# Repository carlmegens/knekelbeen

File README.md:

# Knekelbeen 💀

Een pratende Halloween-schedel die in de slingerkast van een oude wandklok
woont. Hij praat in het Nederlands met de kinderen aan de deur, beweegt zijn
kaak mee met wat hij zegt, kijkt rond, laat zijn ogen gloeien en zet de kaarsen
om hem heen aan het flakkeren. Komt er iemand aan, dan begroet hij die zelf.

```
 kinderen ──► microfoon in de klok ──► schedel (ESP32-S3) ──wifi──► laptop-app ──► Gemini Live
                                            ▲                                          │
 kaak · ogen · kaarsen · nek ◄── speaker ◄──┴──────────── stem (audio over UDP) ◄──────┘
```

De schedel zelf doet de hardware: geluid afspelen, de servo's, de leds, de
microfoon en de sensor. Het denken gebeurt in de laptop-app, die het geluid
doorstuurt naar Gemini en het antwoord terugstuurt naar de schedel. Zonder
laptop werkt hij ook: dan speelt hij de clips van de SD-kaart af.

## Wat hij kan

- **Praten met de AI:** Gemini Live hoort de kinderen en antwoordt meteen
  hardop. Je kunt kiezen uit de Gemini-stemmen of de zelf ontworpen stem
  "Knekelbeen". Zijn karakter staat in [`brain/persona.txt`](brain/persona.txt),
  zijn moppen in [`brain/jokes.txt`](brain/jokes.txt). Hij luistert alleen naar
  Nederlands en weet dat kinderen niet altijd duidelijk praten.
- **Kaak:** volgt het volume van de stem, met een zachte veerbeweging zodat hij
  niet tegen de aanslag klapt.
- **Hoofd draaien:** kijkt af en toe opzij tijdens het praten.
- **Ogen en kaarsen:** WS2812-ogen en een snoer WS2801-kaarsen die meeflakkeren
  met de stem. Een extra ledje of ledstrip kan op LED 2.
- **Soundboard:** clips en geluidseffecten (klokslag, middernacht, onweer,
  wind, hartslag, krakende deur, uil) op de SD-kaart, met een knop per geluid.
  Effecten (`fx_*.wav`) bewegen de kaak niet.
- **Bezoekers merken:** een PIR- of radarsensor op de PIR-aansluiting laat de
  ogen flitsen en de AI een groet uitspreken.
- **Eigen microfoon:** een INMP441 in de klok, zodat de laptop niet bij de deur
  hoeft te staan.

## Hardware

Een eigen printplaat ([`pcb/`](pcb/)) met een ESP32-S3-DevKitC-1 (N8R8) erop
geprikt. Alles wat van de print af gaat, zit aan een schroefklem.

| Onderdeel | Pin(nen) | Aansluiting |
|---|---|---|
| Kaakservo | GPIO 4 | KAAK |
| Draaiservo (nek) | GPIO 8 | DRAAI |
| Ogen, WS2812 | GPIO 15 | OGEN |
| Kaarsen, WS2801 | data 11, klok 12 | KAARSEN |
| LED 2, WS2812 | GPIO 48 | LED 2 |
| PIR of radar | GPIO 2 (hoog = beweging) | PIR |
| 2× versterker DFR0954 (I2S) | BCLK 5, LRC 6, DIN 7; aan/uit 10 (L) en 9 (R) | SPEAKER L/R |
| Microfoon INMP441 (I2S) | WS 16, SCK 17, SD 18 | MIC |
| microSD (SPI) | SCK 13, MISO 14, MOSI 21, CS 47 | op de print |

**De schedel** is de [Robot Skull (Like Geoff off Craig Ferguson)](https://www.printables.com/model/471773-robot-skull-like-geoff-off-craig-ferguson)
van Geoff Williams op Printables (CC BY-SA). Op ware grootte geprint is hij
8,4 cm breed, 11,5 cm diep en 9,4 cm hoog: ongeveer half zo groot als een echte
schedel. Alleen de schedel en de wervel zijn geprint.

De pinnen staan in [`firmware/include/config.h`](firmware/include/config.h).
Voeding: een aparte 5 V-voeding voor de versterkers, servo's en leds.

## In de repo

| Map | Wat |
|---|---|
| [`firmware/`](firmware/) | PlatformIO-project voor de ESP32-S3, inclusief de webpagina van de schedel |
| [`brain/`](brain/) | De laptop-app: bediening, AI (Gemini Live, of Whisper + Claude + Piper) |
| [`clips/`](clips/) | De clips en geluidseffecten, met de teksten in `lines.txt` |
| [`tools/`](tools/) | Clips maken, effecten synthetiseren, uploaden, de microfoon testen |
| [`pcb/`](pcb/) | De printplaat (KiCad, door scripts gegenereerd) en de gerbers |
| [`case/`](case/) | Het geprinte kastje voor de print (OpenSCAD) |
| [`kaarsen/`](kaarsen/) | De geprinte kaarsen voor de WS2801-ledjes |
| [`nek/`](nek/) | De draaiende nek: Fusion-ontwerp, STL's, schroeven en montage |
| [`radar/`](radar/) | ESPHome-config voor de Seeed MR24HPC1-radar als bezoekerssensor |
| [`docs/`](docs/) | De ontwerpopdracht voor de nek, ideeën en het camera-plan |
| `voices/` | Piper-stemmen (niet in git) en de ID van de ontworpen Gemini-stem |

## Aan de slag

### 1. Firmware

Zet je wifi in `firmware/include/secrets.h`; kopieer daarvoor
`secrets.example.h`. Lukt verbinden niet, dan start de schedel een eigen
netwerk `TalkingSkull`.

```
python -m venv .venv && .venv/bin/pip install platformio
cd firmware
../.venv/bin/pio run -e usb -t upload    # de eerste keer, via de native USB-poort
../.venv/bin/pio run -e ota -t upload    # daarna via wifi
```

Daarna is de schedel te bedienen op `http://skull.local` (of zijn IP-adres).
Meer, ook over flashen en Tailscale, in [`firmware/README.md`](firmware/README.md).

### 2. Laptop-app

```
.venv/bin/pip install aiohttp anthropic google-genai numpy faster-whisper piper-tts
echo 'GEMINI_API_KEY=...' > .env         # nooit committen
.venv/bin/python brain/app.py            # of: systemctl --user start skull-brain
```

Open `http://localhost:8000`. De browser staat de microfoon alleen toe op
localhost, daarom draait de bediening met AI op de laptop. Met `SKULL=<ip>`
wijs je een andere schedel aan.

Handige omgevingsvariabelen: `SKULL_GEMINI_MODEL`, `SKULL_GEMINI_VOICE`,
`SKULL_WHISPER` en voor de Claude-modus `ANTHROPIC_API_KEY`. Met
`SKULL_CAM` en `SKULL_CAM_KEY` (een Thingino-camera bij de deur) ziet
Knekelbeen de kinderen bij de begroeting; zie
[`docs/vision-plan.md`](docs/vision-plan.md).

### 3. Clips en effecten

```
tools/gemini_clip.py welkom "Welkom, kleintjes..." --style "fluisterend" --upload
tools/gemini_clip.py --batch clips/lines.txt --upload   # alles uit lines.txt
tools/make_fx.py --upload                               # de geluidseffecten
tools/upload.sh clips/iets.wav                          # een los bestand
tools/make_cues.py --upload                             # lichteffecten in de clips
```

Clips brengen hun eigen lichteffecten mee: `clips/cues.txt` zegt per clip
wanneer de kaarsen opflakkeren, uitgaan of spookgroen worden, wanneer de ogen
flitsen en wanneer de bliksem inslaat (`bliksem`: één inslag, `donder`: een
rollend onweer over kaarsen, ogen en LED 2). `make_cues.py` vindt die zelf (op woorden als "boe" en "geest", en op
de klappen in de geluidseffecten); pas het bestand gerust met de hand aan.
Upload een nieuwe of aangepaste clip daarna met `make_cues.py --upload <naam>`,
anders speelt hij zonder effecten.

Clips worden opgeslagen als 22,05 kHz mono en op loudness genormaliseerd.

### 4. Instellingen bewaren

```
tools/settings.py              # wat staat aan en uit
tools/settings.py --save       # alles naar config/instellingen.json
tools/settings.py --restore    # en weer terug, bijvoorbeeld na een nieuwe flash
```

### 5. Microfoon testen

```
tools/mic_test.py            # 4 s stil, dan 6 s praten: ruis, verschil, storingen
```

Boven de 25 dB verschil tussen spraak en ruis is prima.

## Twee bedieningspagina's

De schedel heeft een eigen pagina (`firmware/web/index.html`, ingebakken in de
firmware) en de laptop-app heeft er een (`brain/index.html`). Elke instelling
hoort op allebei. De pagina van de schedel werkt ook zonder laptop.

## Geheimen

Niet in git: `.env` (API-sleutels), `firmware/include/secrets.h` (wifi),
`radar/secrets.yaml`, de Piper-stemmodellen en eigen opnames
(`clips/opname*.wav`, `clips/raw/`).

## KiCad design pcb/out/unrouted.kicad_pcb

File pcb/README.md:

# Knekelbeen carrier board

A 100 × 96 mm, 2-layer, all through-hole board. The ESP32-S3-DevKitC-1, the
microSD module and the
DFR0954 amps plug onto it, and everything else connects with screw terminals.
The pins match `firmware/include/config.h`.

## Rebuilding

```
source kienv.sh             # only needed while KiCad isn't installed with pacman
python3 make_footprints.py  # ESP32 + DFR0954 footprints -> skull.pretty/
python3 build_board.py      # placement, nets, labels, skull art -> skull.kicad_pcb (unrouted)
python3 route.py            # Freerouting (heavy on the CPU for a few minutes), GND pour
python3 art.py              # only to redraw the skull art on an already routed board
kicad-cli pcb drc -o out/drc.rpt skull.kicad_pcb
```

`out/skull-jlcpcb.zip` holds the gerbers and drill files for ordering.

## Ordering at JLCPCB

1. Go to jlcpcb.com → **Order now** → **Add gerber file** → upload `out/skull-jlcpcb.zip`.
2. Keep the defaults: 2 layers, FR-4, 1.6 mm, HASL, 1 oz copper. Quantity 5 is the minimum.
   A colour other than green costs the same at most sizes. Black looks good on a Halloween prop.
3. Leave **PCB Assembly** off. You solder it yourself, and everything is through-hole.
4. Pick DHL/FedEx shipping for about 5–8 days. Standard shipping is cheaper but takes 2–3 weeks.

## Parts list

Checked against TinyTronics on 2026-10-13 (product codes in brackets; check
stock before ordering). `tools/tinytronics-cart.js` adds all TinyTronics parts
to your cart in one go. TinyTronics has no 3.5 mm pitch screw terminals, so
those come from Domoticx (KF350, €0.27 each) or Kiwi Electronics.

| Ref | Part | Qty | Where | Notes |
|---|---|---|---|---|
| U1 | ESP32-S3-DevKitC-1 | 1 | you have it | |
| — | Female header 40-pin, 2.54 mm | 2 | TinyTronics (40PFEMALEWHITE or -GREEN; the black 40PFEMALE was 2–4 weeks) | cut to 2× 22 for U1; the rest for the amps |
| A1, A2 | DFRobot DFR0954 amp | 2 | you have 1 | A2 can stay empty for now |
| U2 | SN74AHCT125N (DIP-14) | 1 | TinyTronics (SN74AHCT125N) | must be **AHCT** |
| — | IC socket 14-pin | 1 | TinyTronics (14PSOCKET) | |
| J3, J4, J5 | Screw terminal 2-pin, 5.08 mm | 3 | TinyTronics (2PTERM) | 5V IN, SPEAKER L, SPEAKER R |
| J6, J7, J9 | Screw terminal 3-pin, **3.5 mm** | 4 | Domoticx (KF350-3.5 3-pole) | they click together: MIC = 3+3, OGEN 3, LED 2 3 |
| J8 | Screw terminal 2-pin, **3.5 mm** | 2 | Domoticx (KF350-3.5 2-pole) | KAARSEN = 2+2 |
| J10–J13 | Male pin header 1×40, 2.54 mm | 1 | TinyTronics | cut to 3, 3, 3, 9 pins |
| — | microSD module with level shifter | 1 | TinyTronics (000375) | runs on 5 V |
| J14 | Female header 1×6, 2.54 mm, **right-angle** | 1 | Domoticx (CON-2329-P16FH, "horizontaal") | TinyTronics only has straight ones |
| F1 | PTC fuse 5 A, through-hole | 1 | TinyTronics (PPTC5000MATH) | no 4 A available; 5 A is fine. Its legs are ~10 mm apart: bend them in to the 5.1 mm footprint, and keep the body off neighbouring parts (it gets hot when tripped) |
| D1 | 1N5822 Schottky | 1 | TinyTronics (1N5822) | stripe = K |
| D2 | 1N5817 or **1N5819** Schottky | 1 | TinyTronics diode set (DIODESET, has 10× 1N5819) | stripe = K |
| C1 | 1000 µF 25 V, Ø10 mm, 5 mm pitch | 1 | TinyTronics (AISHI 1000uF 25V - 5 pieces, 008079) | mind the polarity |
| C3, C4 | 470 µF 25 V, Ø8 mm, 3.5 mm pitch | 2 | TinyTronics (AISHI 470uF 25V - 5 pieces, 008081) | mind the polarity |
| C2 | Ceramic capacitor 100 nF | 1 | TinyTronics | 5 mm holes; bend the legs if it has 2.54 mm pitch |
| R1 | Resistor 1 kΩ | 1 | TinyTronics (1kΩ 1/4W - 10 pieces, 007621) | |
| R2–R5 | Resistor 330 Ω | 4 | TinyTronics (330Ω 1/4W - 10 pieces, 007619) | |
| LED1 | LED 3 mm green | 1 | TinyTronics | long leg = + (round pad) |
| H1–H4 | M3 spacers + screws | 4 | TinyTronics (M3 spacer kit or 10 mm spacers) | |
| J2 | DC barrel jack, PCB | 1 | skip it | TinyTronics' jacks don't match this footprint; use 5V IN |

## Pin assignments

| Function | GPIO |
|---|---|
| Jaw servo / turn servo | 4 / 8 |
| I2S BCLK / LRC / DIN (both amps) | 5 / 6 / 7 |
| Amp L / amp R shutdown (SD) | 10 / 9 — input = amp on, output low = amp off |
| | Both amps play the L+R mix (the DFR0954's default 680 kΩ on SD), so "L" and "R" are only names. Output high = left channel only. |
| Eyes WS2812 (via 74AHCT125) | 15 |
| Candles WS2801 data / clock (via 74AHCT125) | 11 / 12 |
| LED 2 (via 74AHCT125) | 48 |
| Mic INMP441 WS / SCK / SD | 16 / 17 / 18 |
| microSD MISO / MOSI / SCK / CS | 14 / 21 / 13 / 47 |
| PIR | 2 |
| Spare header | 1, 39, 40, 41, 42 |

## Soldering tips

Solder the lowest parts first: resistors and diodes, then the IC socket, the
ceramic capacitor, the LED, the headers, the electrolytic capacitors, and the
screw terminals last. Check the polarity of the diodes (stripe = K on the
silkscreen), the electrolytic capacitors (+ pad is square) and the LED. Before
plugging in the ESP32, power the board from 5V and check that there is 5 V
between 5V and GND on the spare header, and about 4.7 V on the DevKit's 5V
pin (after D2).

The microSD module plugs into J14 **upside down**: its parts face the board,
its header points left into J14, and its card slot sits at the right board
edge. It then rests on its own header and card slot, about 2.5 mm above the
board. Don't solder anything else under the outline drawn on the silkscreen.

The ESP32 module's PCB antenna sticks out 6.3 mm past the DevKit's top edge
(the "ANTENNE" box on the silkscreen). The board has no copper under it, and
the microSD module ends 1.8 mm before it. Keep metal and wires away from that
area. That's also why mounting hole H2 is under the module rather than in the
top-right corner.

## Footprint sources

- **ESP32-S3-DevKitC-1:** Espressif's DXF `DXF_ESP32-S3-DevKitC-1_V1_20210312CB`
  gives rows 22.86 mm apart, a 25.40 × 62.87 mm board, and the antenna 6.28 mm
  past the top edge.
- **DFR0954:** DFRobot's drawing gives an 18 × 18 mm module with rows 15.24 mm
  apart.
- **microSD module:** the TinyTronics photo shows, from top to bottom with
  the header on the right and parts up: CS, SCK, MOSI, MISO, VCC, GND.

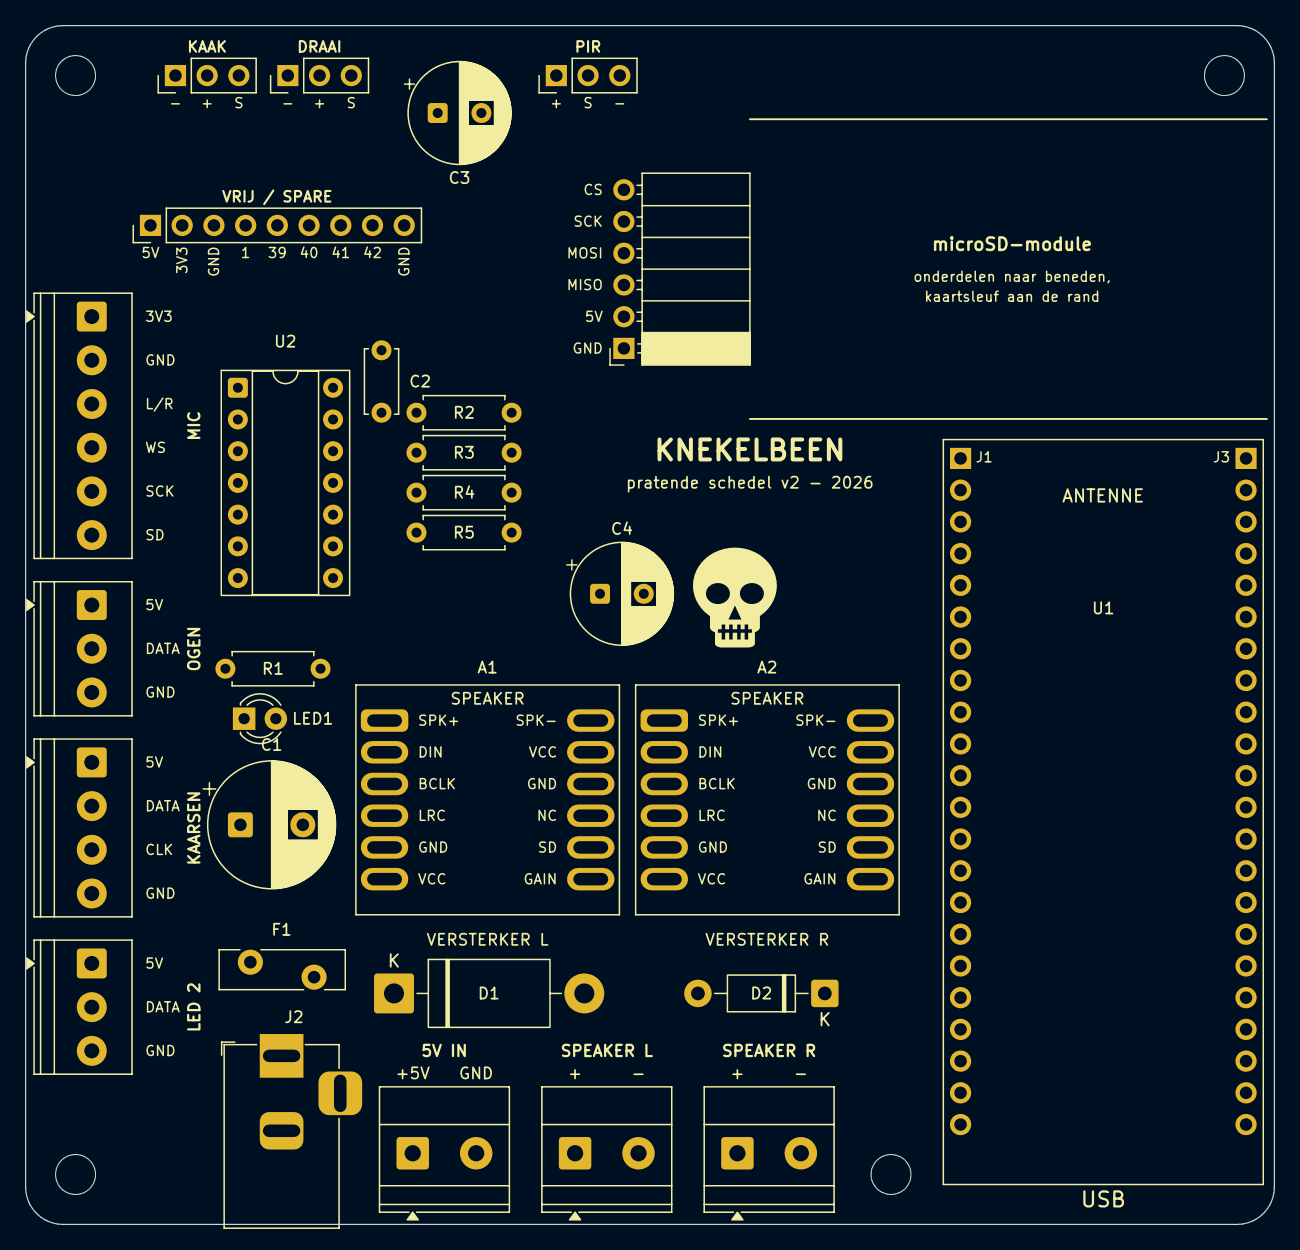
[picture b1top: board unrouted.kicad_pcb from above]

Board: 2 copper layers, 100.0 x 96.0 mm, 34 parts (0 on the bottom side), 42 nets, no tracks yet.

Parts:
A1, A2: DFR0954
C1: 1000uF 10V; CP_Radial_D10.0mm_P5.00mm
C2: 100nF; C_Disc_D5.0mm_W2.5mm_P5.00mm
C3, C4: 470uF 10V; CP_Radial_D8.0mm_P3.50mm
D1: 1N5822; D_DO-201AD_P15.24mm_Horizontal
D2: 1N5817; D_DO-41_SOD81_P10.16mm_Horizontal
F1: PTC 4A (MF-RG400); Fuse_Bourns_MF-RG400
H1, H2, H3, H4: M3; MountingHole_3.2mm_M3
J2: DC 5.5x2.1; BarrelJack_Horizontal
J3: 5V IN; TerminalBlock_Phoenix_MKDS-1,5-2-5.08_1x02_P5.08mm_Horizont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
J4: SPEAKER L; TerminalBlock_Phoenix_MKDS-1,5-2-5.08_1x02_P5.08mm_Horizont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
J5: SPEAKER R; TerminalBlock_Phoenix_MKDS-1,5-2-5.08_1x02_P5.08mm_Horizont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
J6: MIC; TerminalBlock_Phoenix_PT-1,5-6-3.5-H_1x06_P3.50mm_Horizontal
J7: OGEN; TerminalBlock_Phoenix_PT-1,5-3-3.5-H_1x03_P3.50mm_Horizontal
J8: KAARSEN; TerminalBlock_Phoenix_PT-1,5-4-3.5-H_1x04_P3.50mm_Horizontal
J9: LED 2; TerminalBlock_Phoenix_PT-1,5-3-3.5-H_1x03_P3.50mm_Horizontal
J10: SERVO KAAK; PinHeader_1x03_P2.54mm_Vertical
J11: SERVO DRAAI; PinHeader_1x03_P2.54mm_Vertical
J12: PIR; PinHeader_1x03_P2.54mm_Vertical
J13: VRIJ; PinHeader_1x09_P2.54mm_Vertical
J14: SD-KAART; PinSocket_1x06_P2.54mm_Horizontal
LED1: groen; LED_D3.0mm
R1: 1k; R_Axial_DIN0207_L6.3mm_D2.5mm_P7.62mm_Horizontal
R2, R3, R4, R5: 330; R_Axial_DIN0207_L6.3mm_D2.5mm_P7.62mm_Horizontal
U1: ESP32-S3-DevKitC-1
U2: 74AHCT125N; DIP-14_W7.62mm_Socket

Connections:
+3V3: J6.1, J13.2, U1.1, U1.2
+5V: A1.6, A1.8, A2.6, A2.8, C1.1, C2.1, C3.1, C4.1, D1.1, D2.2, F1.2, J7.1, J8.1, J9.1, J10.2, J11.2, J12.1, J13.1, J14.2, R1.1, U2.14
CANDLE_CLK: J8.3, R4.2
CANDLE_DATA: J8.2, R3.2
CCLK_5V: R4.1, U2.8
CDATA_5V: R3.1, U2.6
ESP5V: D2.1, U1.21
EYES_5V: R2.1, U2.3
EYES_DATA: J7.2, R2.2
GND: A1.5, A1.9, A2.5, A2.9, C1.2, C2.2, C3.2, C4.2, D1.2, J2.2, J2.3, J3.2, J6.2, J6.3, J7.3, J8.4, J9.3, J10.1, J11.1, J12.3, J13.3, J13.9, J14.1, LED1.1, U1.22, U1.23, U1.43, U1.44, U2.1, U2.4, U2.7, U2.10, U2.13
IO1: J13.4, U1.26
IO2: J12.2, U1.27
IO4: J10.3, U1.4
IO5: A1.3, A2.3, U1.5
IO6: A1.4, A2.4, U1.6
IO7: A1.2, A2.2, U1.7
IO8: J11.3, U1.12
IO9: A2.11, U1.15
IO10: A1.11, U1.16
IO11: U1.17, U2.5
IO12: U1.18, U2.9
IO13: J14.5, U1.19
IO14: J14.3, U1.20
IO15: U1.8, U2.2
IO16: J6.4, U1.9
IO17: J6.5, U1.10
IO18: J6.6, U1.11
IO21: J14.4, U1.40
IO39: J13.5, U1.31
IO40: J13.6, U1.30
IO41: J13.7, U1.29
IO42: J13.8, U1.28
IO47: J14.6, U1.39
IO48: U1.38, U2.12
LED2_5V: R5.1, U2.11
LED2_DATA: J9.2, R5.2
PWR_LED: LED1.2, R1.2
SPK_L+: A1.1, J4.1
SPK_L-: A1.7, J4.2
SPK_R+: A2.1, J5.1
SPK_R-: A2.7, J5.2
VIN: F1.1, J2.1, J3.1

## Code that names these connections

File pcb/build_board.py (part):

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      pins={1: "+5V", 2: "GND"}, ref_at=(37.1, 65.5))
place("C1", "Capacitor_THT", "CP_Radial_D10.0mm_P5.00mm", 17.2, 52.0, value="1000uF 25V",
      pins={1: "+5V", 2: "GND"}, ref_at=(23.8, 46.8))
place("LED1", "LED_THT", "LED_D3.0mm", 17.5, 43.5, value="groen", pins={1: "GND", 2: "PWR_LED"},
      ref_at=(23.0, 43.5))
place("R1", "Resistor_THT", "R_Axial_DIN0207_L6.3mm_D2.5mm_P7.62mm_Horizontal", 16.0, 39.5,
      value="1k", pins={1: "+5V", 2: "PWR_LED"}, ref_at=(19.81, 39.5))
# Diode into the DevKit's 5V pin: USB plugged in while the 5V supply is on can't backfeed.
place("D2", "Diode_THT", "D_DO-41_SOD81_P10.16mm_Horizontal", 64.0, 65.5, rot=180, value="1N5817",
      pins={1: "ESP5V", 2: "+5V"}, ref_at=(58.92, 65.5))

# ---------------------------------------------------------------- amps + speakers
amp = {"BCLK": "IO5", "LRC": "IO6", "DIN": "IO7"}
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# ---------------------------------------------------------------- level shifter
# 74AHCT125: 3.3 V GPIO in, clean 5 V out for the LED data lines. OE pins low = on.
place("U2", "Package_DIP", "DIP-14_W7.62mm_Socket", 17.0, 17.0, value="74AHCT125N",
      pins={1: "GND", 2: "IO15", 3: "EYES_5V", 4: "GND", 5: "IO11", 6: "CDATA_5V", 7: "GND",
            8: "CCLK_5V", 9: "IO12", 10: "GND", 11: "LED2_5V", 12: "IO48", 13: "GND", 14: "+5V"},
      ref_at=(20.8, 13.3))
place("C2", "Capacitor_THT", "C_Disc_D5.0mm_W2.5mm_P5.00mm", 28.5, 14.0, rot=270, value="100nF",
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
